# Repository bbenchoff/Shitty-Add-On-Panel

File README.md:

# Shitty Add-On Panel

This is a tileable 'display' panel that provides 3.3V power through a Shitty Add-On V1.69bis connector.

Panels are 60mm x 60mm and can be connected end-to-end. Holes for M3 standoffs are provided.

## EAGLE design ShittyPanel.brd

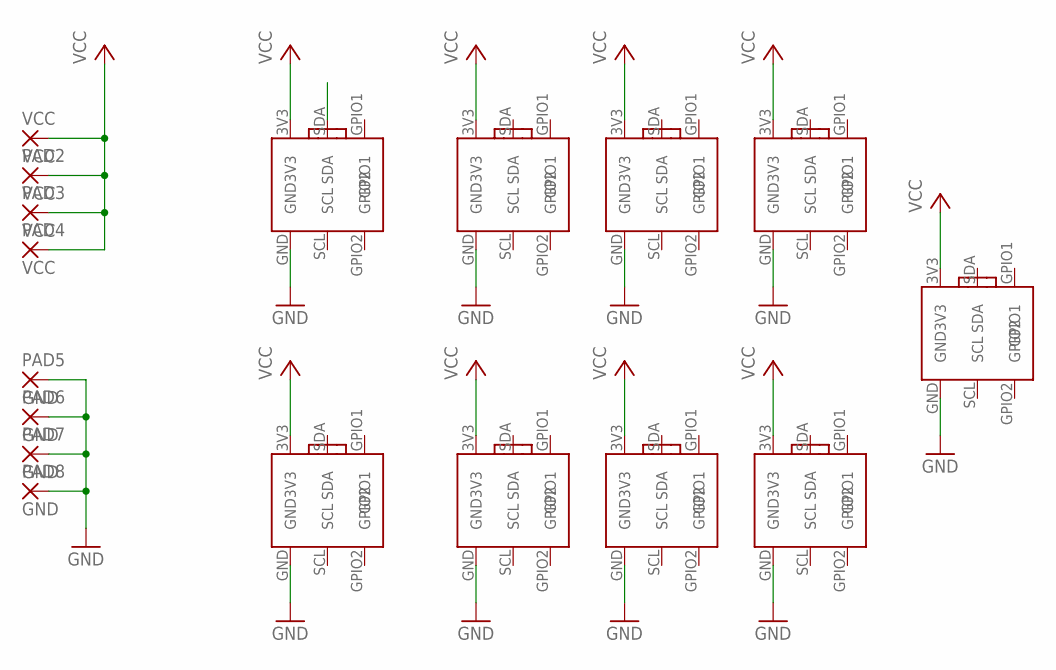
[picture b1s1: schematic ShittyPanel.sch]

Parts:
PAD2, PAD3, PAD4: VCC; SMD2,54-5,08
PAD5, PAD6, PAD7, PAD8: GND; SMD2,54-5,08
U$1, U$2, U$3, U$4, U$5, U$6, U$7, U$8, U$9: SHITTYADDON2
VCC: VCC; SMD2,54-5,08

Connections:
GND: PAD5.1, PAD6.1, PAD7.1, PAD8.1, U$1.GND, U$2.GND, U$3.GND, U$4.GND, U$5.GND, U$6.GND, U$7.GND, U$8.GND, U$9.GND
VCC: PAD2.1, PAD3.1, PAD4.1, U$1.3V3, U$2.3V3, U$3.3V3, U$4.3V3, U$5.3V3, U$6.3V3, U$7.3V3, U$8.3V3, U$9.3V3, VCC.1

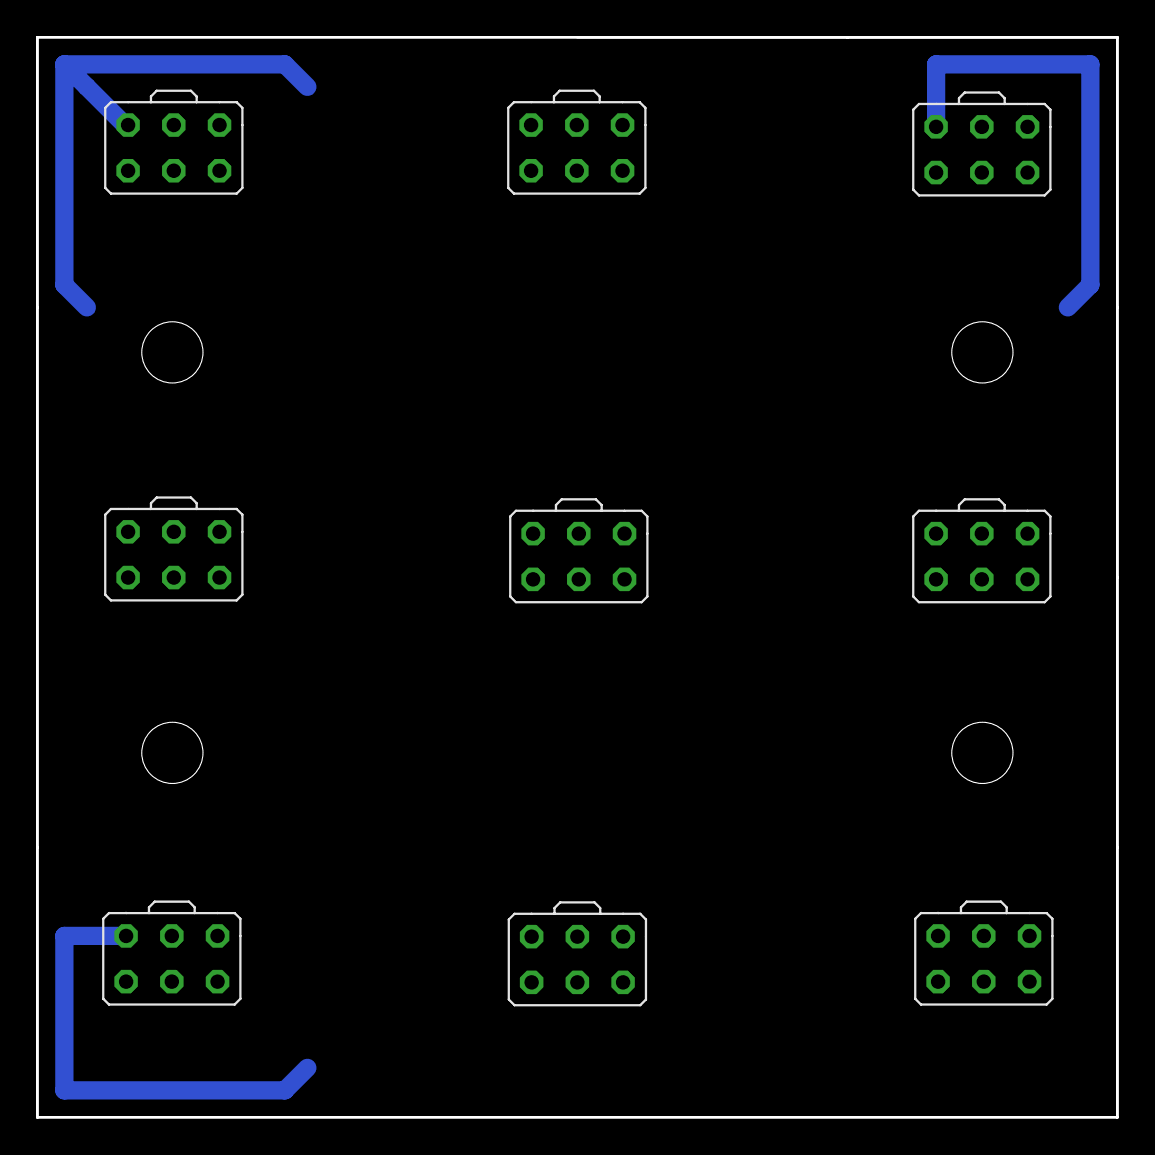
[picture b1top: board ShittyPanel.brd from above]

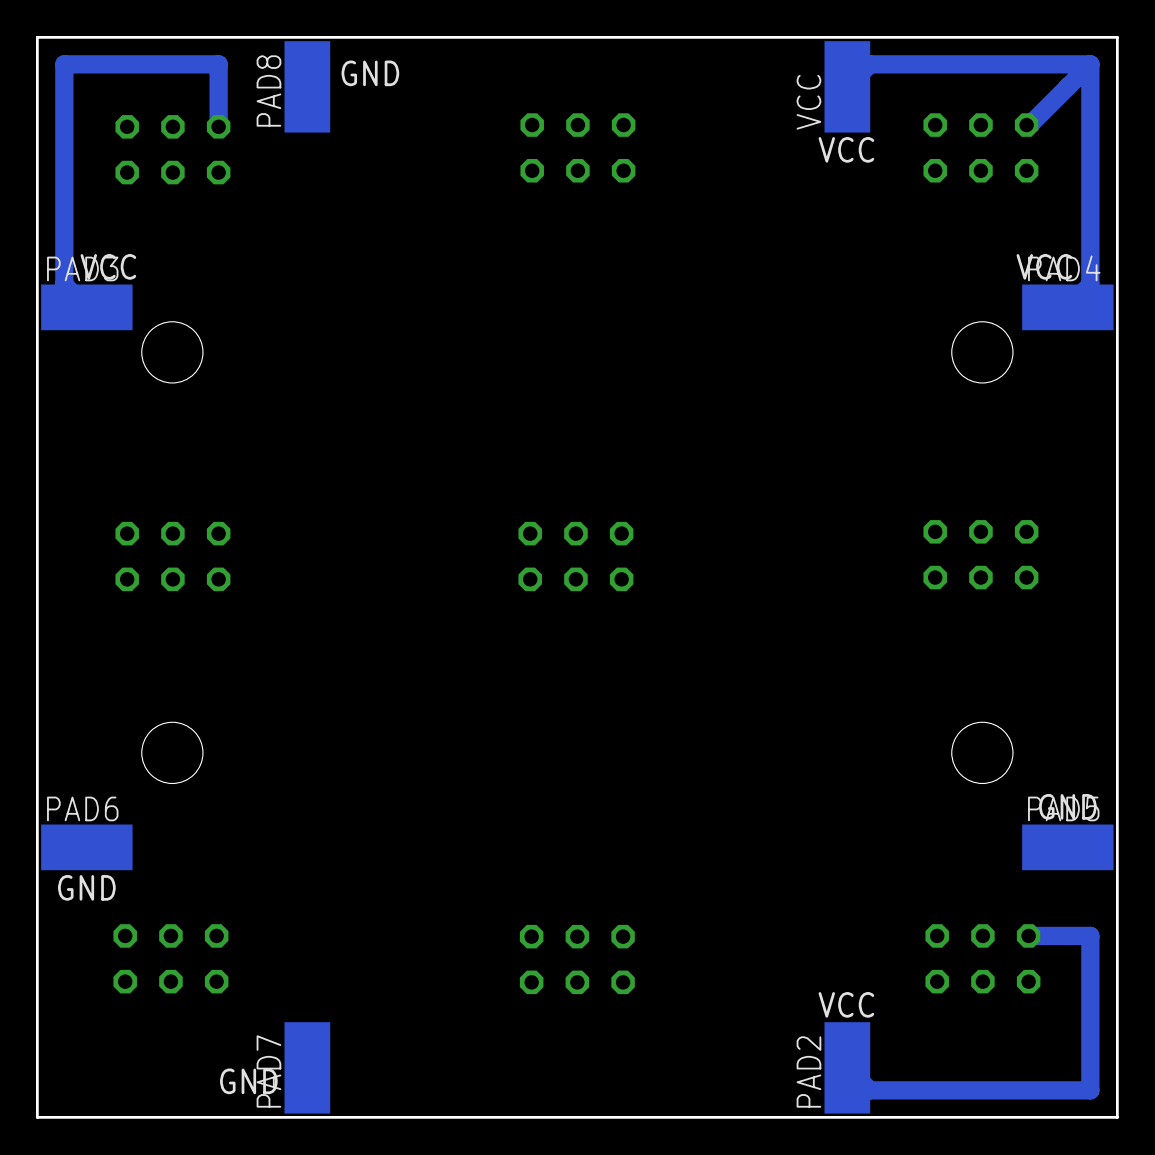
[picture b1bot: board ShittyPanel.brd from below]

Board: 2 copper layers, 60.0 x 60.0 mm, 17 parts (8 on the bottom side), 2 nets.

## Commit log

2019-07-24 Initial
    Added eagle sch brd and gerbers
